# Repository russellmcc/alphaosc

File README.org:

* What is this?

This repository includes the design files and code for a eurorack-format digital audio oscillator.

* What's special about this digital oscillator?

Unlike other digital oscillators, this has very low aliasing.  This is achieved by running at a very high sampling rate (megahertz range, depending on target output pitch).

Also, many unusual waveforms, such as "comb" waveforms or "variable pulse saw" waveforms can be output.

The basic design and the output waveforms available are inspired closely (but not precisely) by Roland's Alpha Juno line of synthesizers.

* Project structure

The four-layer circuit board was designed using [[http://kicad-pcb.org][kicad]] and is available in the ~pcb~ subfolder.

Code for the arduino (which is reponsible for interfacing with the A/D converter for CV signals) is in the ~arduino~ folder.

Code for the fpga is written in [[https://clash-lang.org][clash]] and available in the ~src~ folder.

Panel design files are in the ~panel~ folder.

Scripts to design the tuning table are in the ~design~ folder.

This is the code for a digital oscillator core of a hardware synthesizer NCO developed in clash and arduino.  The oscillator is inspired by the Alpha Juno line of synthesizers by Roland.

* Tips for building/running

Note that this is a fairly advanced build and should be considered a "build at your own risk" type affair.

verilog code for the FPGA can be built by running the ~build.sh~ script in the ~src~ folder.  To program the FPGA, you'll need to use Lattice's tools available on [[http://www.latticesemi.com][their website]].  Note that you'll also need to include the ~lattice_alpha.lpf~ which locates the pins.

To run the test suite for the FPGA code, run ~test.sh~ in the ~src~ folder.

Note that some fuses on the arduino need to be set, specifically the "clock out" fuse.  This can be programmed with the following one-liner:

#+begin_src bash
avrdude -c avrispmkii -p m328p -U lfuse:w:0xB7:m
#+end_src

* License

Distributed under the terms of the GPLv3 (available in COPYING).  By contributing to this project, you agree to license your contribution under those terms.

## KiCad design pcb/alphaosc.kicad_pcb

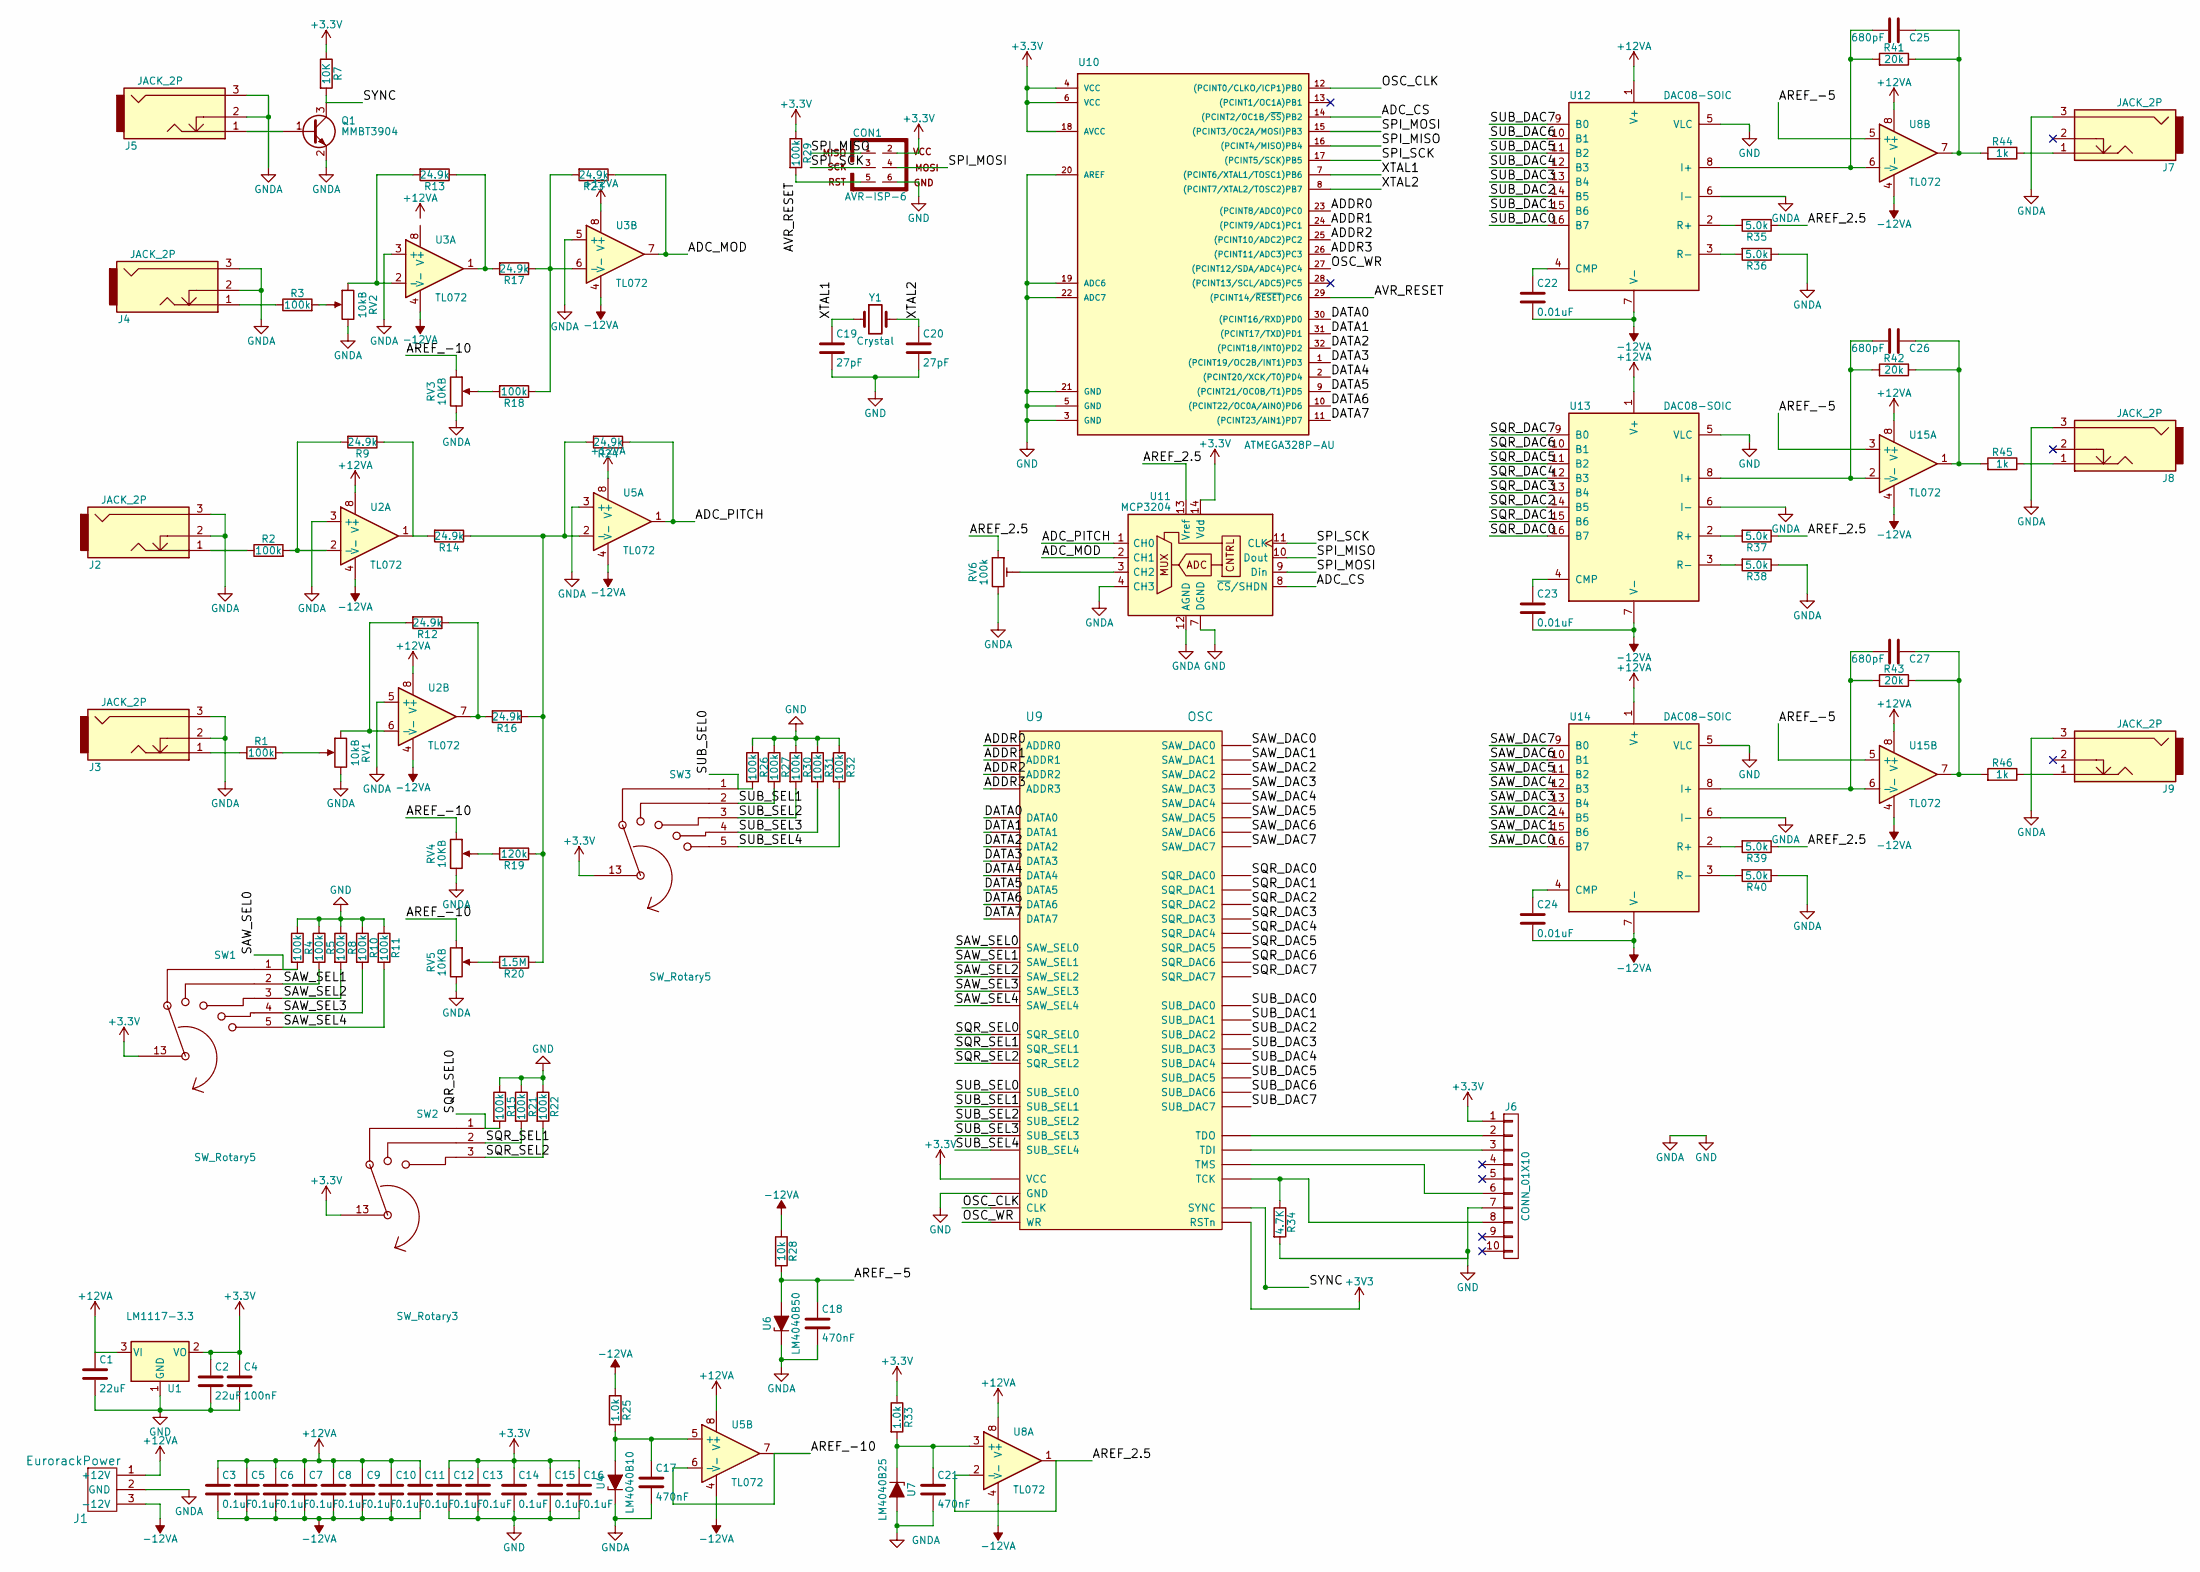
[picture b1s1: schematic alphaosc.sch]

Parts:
C1, C2: 22uF; C_0603
C3, C5, C6, C7, C8, C9, C10, C11, C12, C13, C14, C15, C16: 0.1uF; C_0603
C4: 100nF; C_0603
C17, C18, C21: 470nF; C_0603
C19, C20: 27pF; C_0603
C22, C23, C24: 0.01uF; C_0603
C25, C26, C27: 680pF; C_0603
CON1: AVR-ISP-6; Pin_Header_Straight_2x03_Pitch2.54mm
J1: EurorackPower; EurorackPower10
J2, J3, J4, J5, J7, J8, J9: JACK_2P; THONKICONN
J6: CONN_01X10; Pin_Header_Straight_1x10_Pitch2.54mm
Q1: MMBT3904; SOT-23
R1, R2, R3, R4, R5, R8, R10, R11, R15, R18, R21, R22, R26, R27, R29, R30, R31, R32: 100k; R_0603
R7: 10K; R_0603
R9, R12, R13, R14, R16, R17, R23, R24: 24.9k; R_0603
R19: 120k; R_0603
R20: 1.5M; R_0603
R25, R33: 1.0k; R_0603
R28: 10k; R_0603
R34: 4.7K; R_0603
R35, R36, R37, R38, R39, R40: 5.0k; R_0603
R41, R42, R43: 20k; R_0603
R44, R45, R46: 1k; R_0603
RV1, RV2: 10kB; Potentiometer_Bourns_PTV09A-1_Horizontal
RV3, RV4, RV5: 10KB; Potentiometer_Bourns_PTV09A-1_Horizontal
RV6: 100k; Potentiometer_Trimmer_Vishay_T73YP_Horizontal
SW1, SW3: SW_Rotary5; Alps_SRBV
SW2: SW_Rotary3; Alps_SRBV
U1: LM1117-3.3; SOT-223
U2, U3, U5, U8, U15: TL072; SOIC-8_3.9x4.9mm_Pitch1.27mm
U4: LM4040B10; SOT-23
U6: LM4040B50; SOT-23
U7: LM4040B25; SOT-23
U9: OSC; LAMXO256C-3TN100E
U10: ATMEGA328P-AU; TQFP-32_7x7mm_Pitch0.8mm
U11: MCP3204; SOIC-14_3.9x8.7mm_Pitch1.27mm
U12, U13, U14: DAC08-SOIC; SOIC-16_3.9x9.9mm_Pitch1.27mm
Y1: Crystal; Crystal_SMD_HC49-SD

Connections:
+12VA: C1.1, C3.1, C5.1, C6.1, C7.1, C8.1, C9.1, C10.1, C11.1, J1.1 (+12V), U1.3 (VI), U2.8 (V+), U3.8 (V+), U5.8 (V+), U8.8 (V+), U12.1 (V+), U13.1 (V+), U14.1 (V+), U15.8 (V+)
-12VA: C3.2, C5.2, C6.2, C7.2, C8.2, C9.2, C10.2, C11.2, C22.2, C23.2, C24.2, J1.3 (-12V), R25.1, R28.1, U2.4 (V-), U3.4 (V-), U5.4 (V-), U8.4 (V-), U12.7 (V-), U13.7 (V-), U14.7 (V-), U15.4 (V-)
/ADC_CS: U10.14 ((PCINT2/OC1B/~SS~)PB2), U11.8 (~CS~/SHDN)
/ADC_MOD: R23.1, U3.7, U11.2 (CH1)
/ADC_PITCH: R24.1, U5.1, U11.1 (CH0)
/ADDR0: U9.67 (ADDR0), U10.23 ((PCINT8/ADC0)PC0)
/ADDR1: U9.65 (ADDR1), U10.24 ((PCINT9/ADC1)PC1)
/ADDR2: U9.63 (ADDR2), U10.25 ((PCINT10/ADC2)PC2)
/ADDR3: U9.64 (ADDR3), U10.26 ((PCINT11/ADC3)PC3)
/AREF_2.5: R35.1, R37.1, R39.1, RV6.1, U8.1, U8.2 (-), U11.13 (Vref)
/AREF_-5: C18.1, R28.2, U6.2 (A), U8.5 (+), U15.3 (+), U15.5 (+)
/AREF_-10: RV3.1, RV4.1, RV5.1, U5.6 (-), U5.7
/AVR_RESET: CON1.5, R29.2, U10.29 ((PCINT14/~RESET~)PC6)
/DATA0: U9.70 (DATA0), U10.30 ((PCINT16/RXD)PD0)
/DATA1: U9.69 (DATA1), U10.31 ((PCINT17/TXD)PD1)
/DATA2: U9.16 (DATA2), U10.32 ((PCINT18/INT0)PD2)
/DATA3: U9.72 (DATA3), U10.1 ((PCINT19/OC2B/INT1)PD3)
/DATA4: U9.71 (DATA4), U10.2 ((PCINT20/XCK/T0)PD4)
/DATA5: U9.83 (DATA5), U10.9 ((PCINT21/OC0B/T1)PD5)
/DATA6: U9.76 (DATA6), U10.10 ((PCINT22/OC0A/AIN0)PD6)
/DATA7: U9.68 (DATA7), U10.11 ((PCINT23/AIN1)PD7)
/OSC_CLK: U9.36 (CLK), U10.12 ((PCINT0/CLKO/ICP1)PB0)
/OSC_WR: U9.66 (WR), U10.27 ((PCINT12/SDA/ADC4)PC4)
/SAW_DAC0: U9.9 (SAW_DAC0), U14.16 (B7)
/SAW_DAC1: U9.13 (SAW_DAC1), U14.15 (B6)
/SAW_DAC2: U9.59 (SAW_DAC2), U14.14 (B5)
/SAW_DAC3: U9.14 (SAW_DAC3), U14.13 (B4)
/SAW_DAC4: U9.61 (SAW_DAC4), U14.12 (B3)
/SAW_DAC5: U9.58 (SAW_DAC5), U14.11 (B2)
/SAW_DAC6: U9.47 (SAW_DAC6), U14.10 (B1)
/SAW_DAC7: U9.11 (SAW_DAC7), U14.9 (B0)
/SAW_SEL0: R4.2, SW1.1, U9.55 (SAW_SEL0)
/SAW_SEL1: R5.2, SW1.2, U9.56 (SAW_SEL1)
/SAW_SEL2: R8.2, SW1.3, U9.54 (SAW_SEL2)
/SAW_SEL3: R10.2, SW1.4, U9.57 (SAW_SEL3)
/SAW_SEL4: R11.2, SW1.5, U9.19 (SAW_SEL4)
/SPI_MISO: CON1.1, U10.16 ((PCINT4/MISO)PB4), U11.10 (Dout)
/SPI_MOSI: CON1.4, U10.15 ((PCINT3/OC2A/MOSI)PB3), U11.9 (Din)
/SPI_SCK: CON1.3, U10.17 ((PCINT5/SCK)PB5), U11.11 (CLK)
/SQR_DAC0: U9.96 (SQR_DAC0), U13.16 (B7)
/SQR_DAC1: U9.86 (SQR_DAC1), U13.15 (B6)
/SQR_DAC2: U9.80 (SQR_DAC2), U13.14 (B5)
/SQR_DAC3: U9.95 (SQR_DAC3), U13.13 (B4)
/SQR_DAC4: U9.100 (SQR_DAC4), U13.12 (B3)
/SQR_DAC5: U9.87 (SQR_DAC5), U13.11 (B2)
/SQR_DAC6: U9.82 (SQR_DAC6), U13.10 (B1)
/SQR_DAC7: U9.85 (SQR_DAC7), U13.9 (B0)
/SQR_SEL0: R15.2, SW2.1, U9.79 (SQR_SEL0)
/SQR_SEL1: R21.2, SW2.2, U9.73 (SQR_SEL1)
/SQR_SEL2: R22.2, SW2.3, U9.77 (SQR_SEL2)
/SUB_DAC0: U9.39 (SUB_DAC0), U12.16 (B7)
/SUB_DAC1: U9.34 (SUB_DAC1), U12.15 (B6)
/SUB_DAC2: U9.32 (SUB_DAC2), U12.14 (B5)
/SUB_DAC3: U9.38 (SUB_DAC3), U12.13 (B4)
/SUB_DAC4: U9.29 (SUB_DAC4), U12.12 (B3)
/SUB_DAC5: U9.37 (SUB_DAC5), U12.11 (B2)
/SUB_DAC6: U9.30 (SUB_DAC6), U12.10 (B1)
/SUB_DAC7: U9.53 (SUB_DAC7), U12.9 (B0)
/SUB_SEL0: R26.2, SW3.1, U9.45 (SUB_SEL0)
/SUB_SEL1: R27.2, SW3.2, U9.46 (SUB_SEL1)
/SUB_SEL2: R30.2, SW3.3, U9.43 (SUB_SEL2)
/SUB_SEL3: R31.2, SW3.4, U9.44 (SUB_SEL3)
/SUB_SEL4: R32.2, SW3.5, U9.50 (SUB_SEL4)
/SYNC: Q1.3 (C), R7.2, U9.78 (SYNC)
/XTAL1: C19.1, U10.7 ((PCINT6/XTAL1/TOSC1)PB6), Y1.1
/XTAL2: C20.1, U10.8 ((PCINT7/XTAL2/TOSC2)PB7), Y1.2
GND: C1.2, C2.2, C4.2, C12.2, C13.2, C14.2, C15.2, C16.2, C17.2, C18.2, C19.2, C20.2, C21.2, CON1.6, J1.2 (GND), J2.2, J2.3, J3.2, J3.3, J4.2, J4.3, J5.2, J5.3, J6.7, J7.3, J8.3, J9.3, Q1.2 (E), R4.1, R5.1, R8.1, R10.1, R11.1, R15.1, R21.1, R22.1, R26.1, R27.1, R30.1, R31.1, R32.1, R34.2, R36.1, R38.1, R40.1, RV1.3, RV2.3, RV3.3, RV4.3, RV5.3, RV6.3, U1.1 (GND), U2.3 (+), U2.5 (+), U3.3 (+), U3.5 (+), U4.1 (K), U5.3 (+), U6.1 (K), U7.2 (A), U9.12 (GND), U9.25 (GND), U9.40 (GND), U9.42 (GND), U9.62 (GND), U9.75 (GND), U9.84 (GND), U9.93 (GND), U10.3 (GND), U10.5 (GND), U10.19 (ADC6), U10.20 (AREF), U10.21 (GND), U10.22 (ADC7), U11.4 (CH3), U11.7 (DGND), U11.12 (AGND), U12.5 (VLC), U12.6 (I-), U13.5 (VLC), U13.6 (I-), U14.5 (VLC), U14.6 (I-)
unnamed: C17.1, R25.2, U4.2 (A), U5.5 (+)
unnamed: C21.1, R33.2, U7.1 (K), U8.3 (+)
unnamed: C22.1, U12.4 (CMP)
unnamed: C23.1, U13.4 (CMP)
unnamed: C24.1, U14.4 (CMP)
unnamed: C25.1, R41.1, R44.2, U8.7
unnamed: C25.2, R41.2, U8.6 (-), U12.8 (I+)
unnamed: C26.1, R42.1, R45.2, U15.1
unnamed: C26.2, R42.2, U13.8 (I+), U15.2 (-)
unnamed: C27.1, R43.1, R46.2, U15.7
unnamed: C27.2, R43.2, U14.8 (I+), U15.6 (-)
unnamed: J2.1, R2.1
unnamed: J3.1, R1.1
unnamed: J4.1, R3.1
unnamed: J5.1, Q1.1 (B)
unnamed: J6.2, U9.31 (TDO)
unnamed: J6.3, U9.33 (TDI)
unnamed: J6.6, U9.26 (TMS)
unnamed: J6.8, R34.1, U9.28 (TCK)
unnamed: J7.1, R44.1
unnamed: J8.1, R45.1
unnamed: J9.1, R46.1
unnamed: R1.2, RV1.2
unnamed: R2.2, R9.2, U2.2 (-)
unnamed: R3.2, RV2.2
unnamed: R12.1, R16.2, U2.7
unnamed: R12.2, RV1.1, U2.6 (-)
unnamed: R13.1, R17.2, U3.1
unnamed: R13.2, RV2.1, U3.2 (-)
unnamed: R14.1, R16.1, R19.1, R20.1, R24.2, U5.2 (-)
unnamed: R9.1, R14.2, U2.1
unnamed: R17.1, R18.1, R23.2, U3.6 (-)
unnamed: R18.2, RV3.2
unnamed: R19.2, RV4.2
unnamed: R20.2, RV5.2
unnamed: R35.2, U12.2 (R+)
unnamed: R36.2, U12.3 (R-)
unnamed: R37.2, U13.2 (R+)
unnamed: R38.2, U13.3 (R-)
unnamed: R39.2, U14.2 (R+)
unnamed: R40.2, U14.3 (R-)
unnamed: RV6.2, U11.3 (CH2)

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
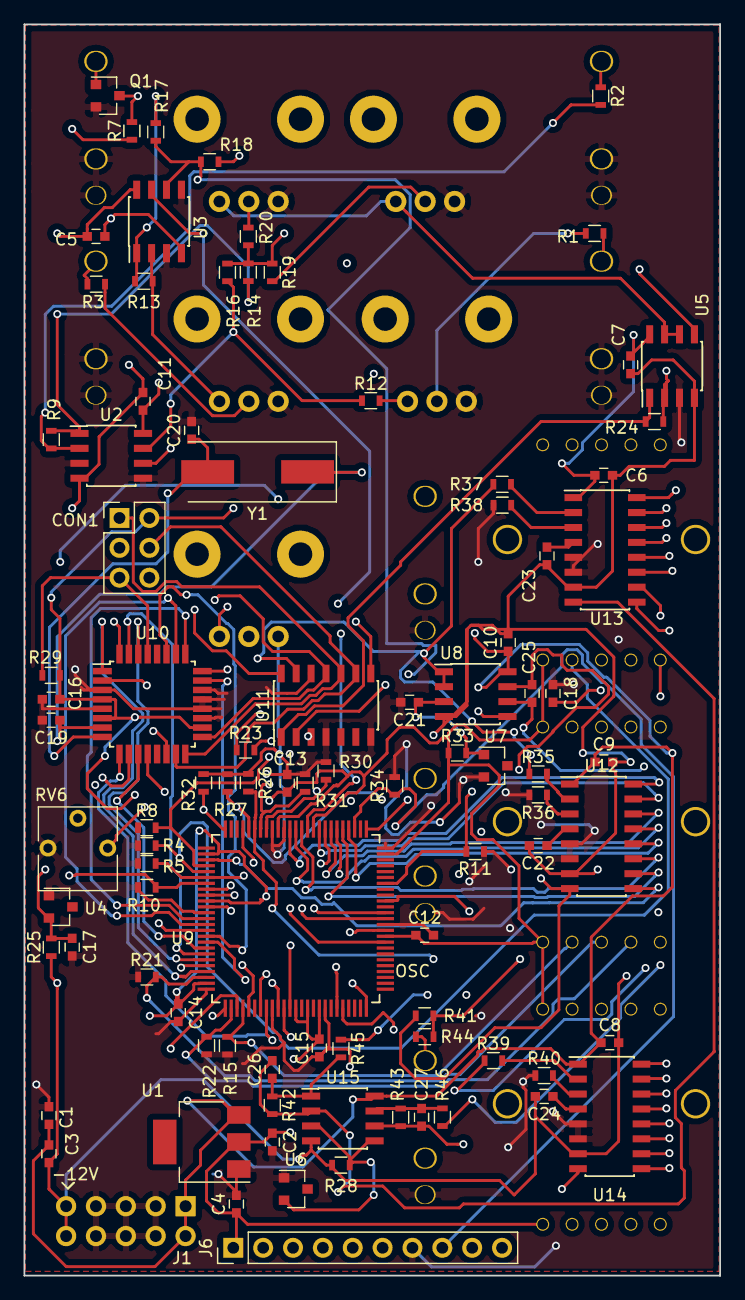
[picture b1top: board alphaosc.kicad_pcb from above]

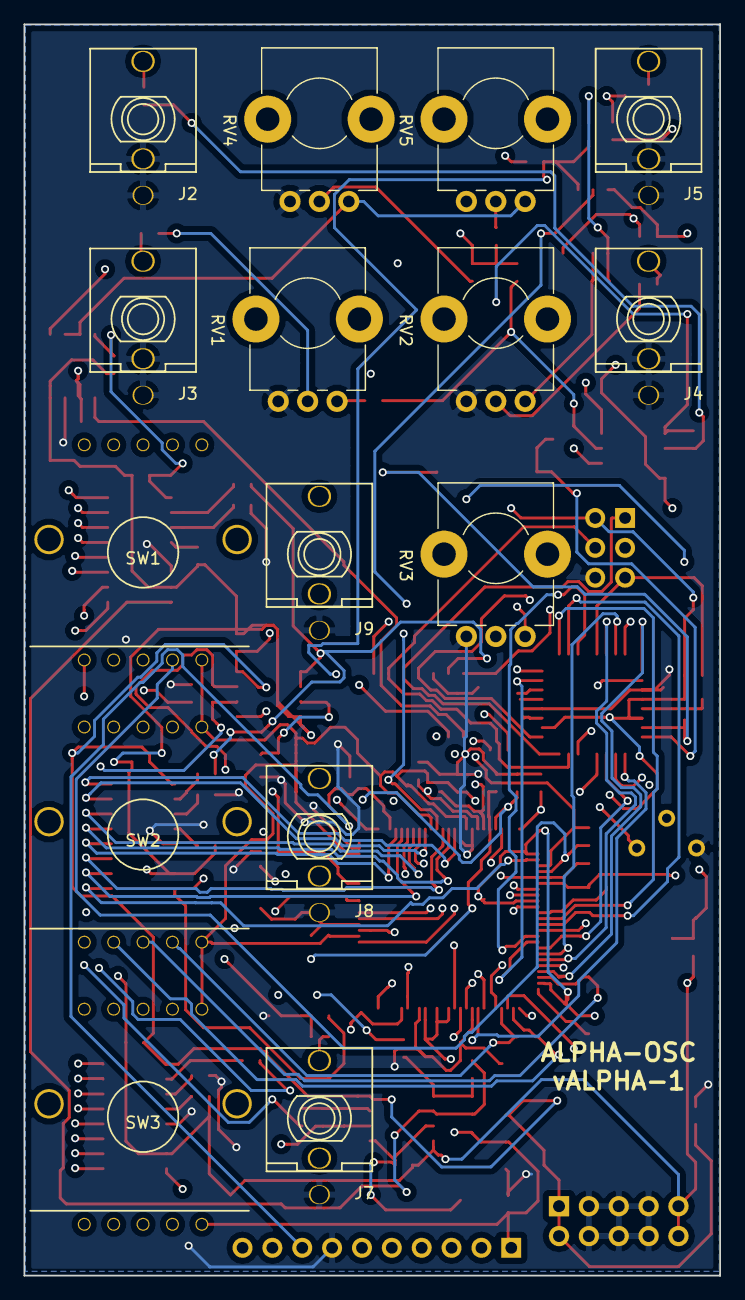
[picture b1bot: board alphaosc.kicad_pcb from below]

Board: 4 copper layers, 59.2 x 106.4 mm, 108 parts (15 on the bottom side), 110 nets.

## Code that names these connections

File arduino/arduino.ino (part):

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
#include <SPI.h>
// SPI: SCK: PB5 - "Digital 13"
// SPI: MISO: PB4 - "Digital 12"
// SPI: MOSI:  PB3 - "Digital 11"
// SS: PB2 - "Digital 10"
const int chipSelectPin = 10;

// ADDR: PortC:0-3
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
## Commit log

2019-06-14 Add notes on tuning trade-offs
2019-06-14 oops typos
2019-06-14 untested travis CI
2019-06-14 maybe this command will work
2019-06-15 bleh...

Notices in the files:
parts and their libraries:
Copyright 2016 Accelerated Designs. All rights reserved.
